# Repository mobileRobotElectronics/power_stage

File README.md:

# power-stage
Power stage designed for a mobile robot during a practical course at Karlsruhe Institute of Technology

This repository includes both the schematic and the PCD design of the power stage. Designed and edited using [KicCad7.0](https://www.kicad.org/).

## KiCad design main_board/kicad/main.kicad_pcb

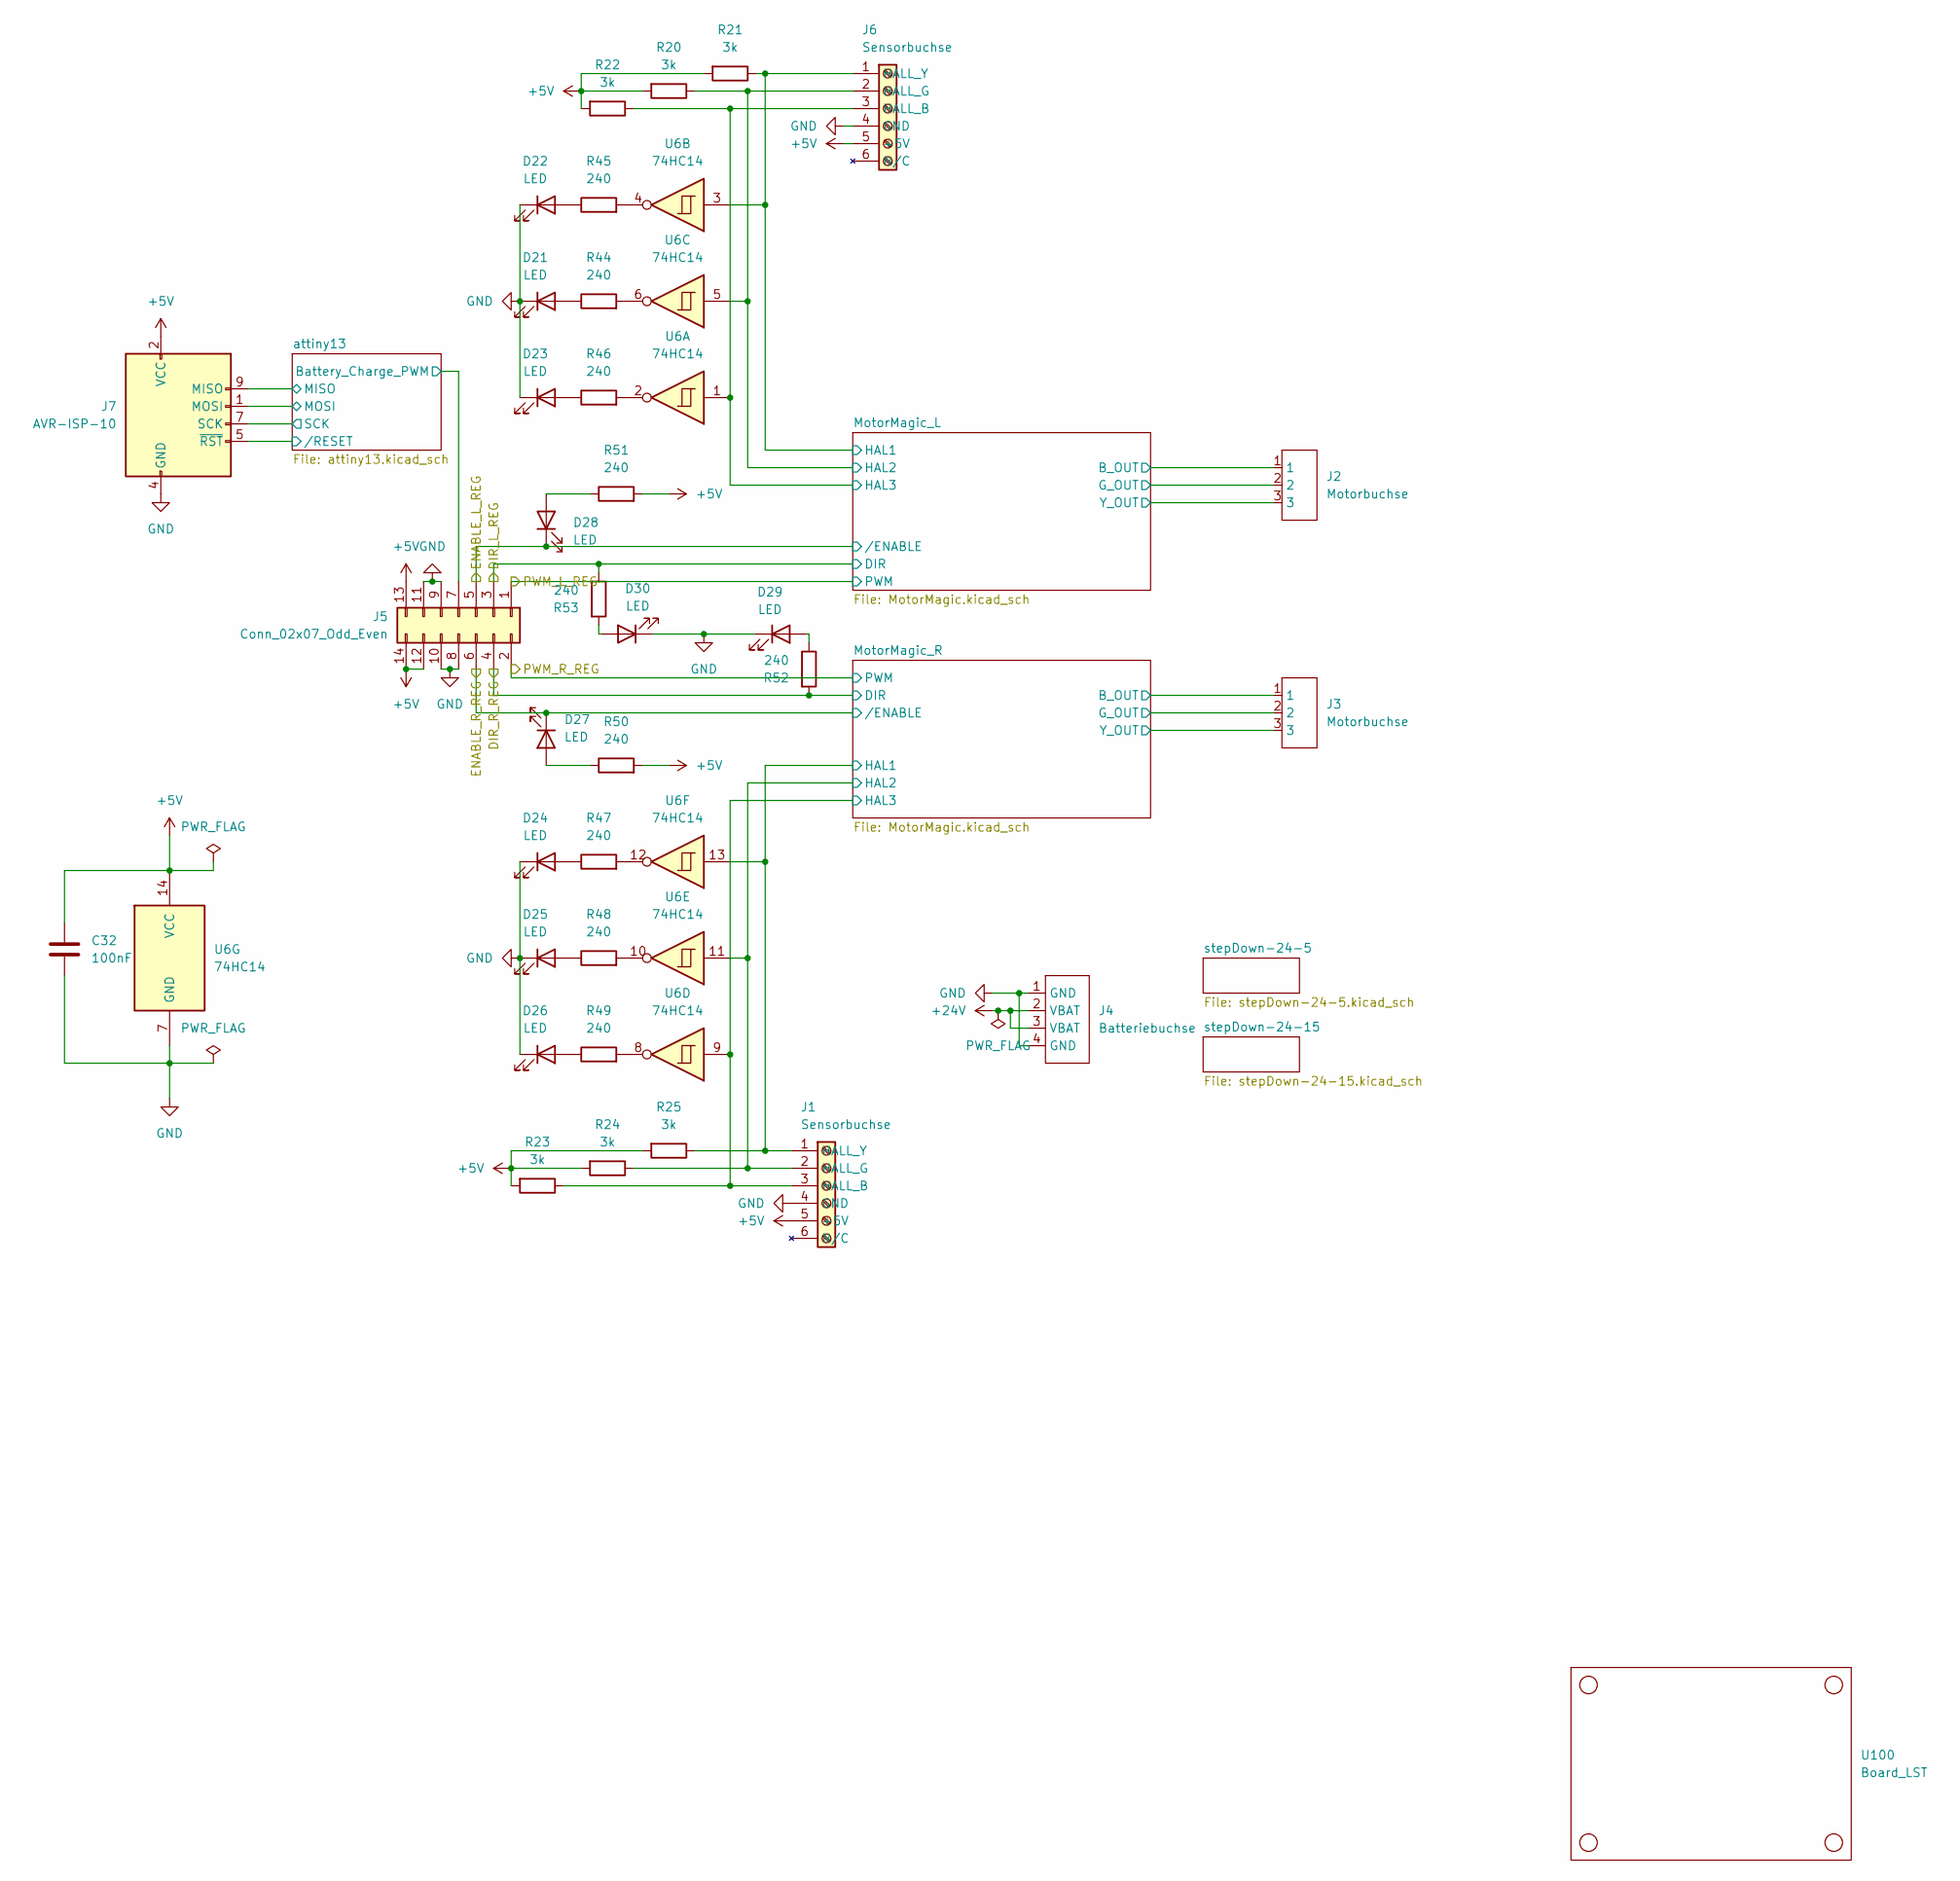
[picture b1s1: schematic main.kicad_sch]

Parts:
C32: 100nF; C_Disc_D3.0mm_W1.6mm_P2.50mm
D21, D22, D23, D24, D25, D26, D27, D28, D29, D30: LED; LED_D5.0mm
J1, J6: Sensorbuchse; PhoenixContact_MC_1,5_6-G-3.81_1x06_P3.81mm_Horizontal
J2, J3: Motorbuchse
J4: Batteriebuchse
J5: Conn_02x07_Odd_Even; IDC-Header_2x07_P2.54mm_Horizontal
J7: AVR-ISP-10; IDC-Header_2x06_P2.54mm_Horizontal
R20, R21, R22, R23, R24, R25: 3k; R_Axial_DIN0207_L6.3mm_D2.5mm_P7.62mm_Horizontal
R44, R45, R46, R47, R48, R49, R50, R51, R52, R53: 240; R_Axial_DIN0207_L6.3mm_D2.5mm_P7.62mm_Horizontal
U6: 74HC14; DIP-14_W10.16mm_LongPads
U100: Board_LST

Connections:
+24V: J4.2 (VBAT), J4.3 (VBAT); also elsewhere on the board
/DIR_L_REG: J5.3, R53.1; also elsewhere on the board
/DIR_R_REG: J5.4, R52.2; also elsewhere on the board
/ENABLE_L_REG: D28.1 (K), J5.5; also elsewhere on the board
/ENABLE_R_REG: D27.1 (K), J5.6; also elsewhere on the board
/MotorMagic_L/B_OUT: J2.1; also elsewhere on the board
/MotorMagic_L/G_OUT: J2.2; also elsewhere on the board
/MotorMagic_L/HAL1: J6.1 (HALL_Y), R21.1, U6.3; also elsewhere on the board
/MotorMagic_L/HAL2: J6.2 (HALL_G), R20.1, U6.5; also elsewhere on the board
/MotorMagic_L/HAL3: J6.3 (HALL_B), R22.1, U6.1; also elsewhere on the board
/MotorMagic_L/Y_OUT: J2.3; also elsewhere on the board
/MotorMagic_R/B_OUT: J3.1; also elsewhere on the board
/MotorMagic_R/G_OUT: J3.2; also elsewhere on the board
/MotorMagic_R/HAL1: J1.1 (HALL_Y), R25.1, U6.13; also elsewhere on the board
/MotorMagic_R/HAL2: J1.2 (HALL_G), R24.1, U6.11; also elsewhere on the board
/MotorMagic_R/HAL3: J1.3 (HALL_B), R23.1, U6.9; also elsewhere on the board
/MotorMagic_R/Y_OUT: J3.3; also elsewhere on the board
/PWM_L_REG: J5.1; also elsewhere on the board
/PWM_R_REG: J5.2; also elsewhere on the board
/attiny13/Battery_Charge_PWM: J5.7, J7.1 (MOSI); also elsewhere on the board
/attiny13/MISO: J7.9 (MISO); also elsewhere on the board
/attiny13/SCK: J7.7 (SCK); also elsewhere on the board
/attiny13//RESET: J7.5 (~RST); also elsewhere on the board
GND: C32.2, D21.1 (K), D22.1 (K), D23.1 (K), D24.1 (K), D25.1 (K), D26.1 (K), D29.1 (K), D30.1 (K), J1.4 (GND), J4.1 (GND), J4.4 (GND), J5.8, J5.9, J5.10, J5.11, J6.4 (GND), J7.4 (GND), J7.6 (GND), J7.8 (GND), J7.10 (GND), U6.7 (GND); also elsewhere on the board
unnamed: D21.2 (A), R44.1
unnamed: D22.2 (A), R45.1
unnamed: D23.2 (A), R46.1
unnamed: D24.2 (A), R47.1
unnamed: D25.2 (A), R48.1
unnamed: D26.2 (A), R49.1
unnamed: D27.2 (A), R50.1
unnamed: D28.2 (A), R51.1
unnamed: D29.2 (A), R52.1
unnamed: D30.2 (A), R53.2
unnamed: R44.2, U6.6
unnamed: R45.2, U6.4
unnamed: R46.2, U6.2
unnamed: R47.2, U6.12
unnamed: R48.2, U6.10
unnamed: R49.2, U6.8

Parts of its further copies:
C16, C22: 100nF; C_Disc_D3.0mm_W1.6mm_P2.50mm

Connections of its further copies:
GND: C16.2, C22.2; also elsewhere on the board

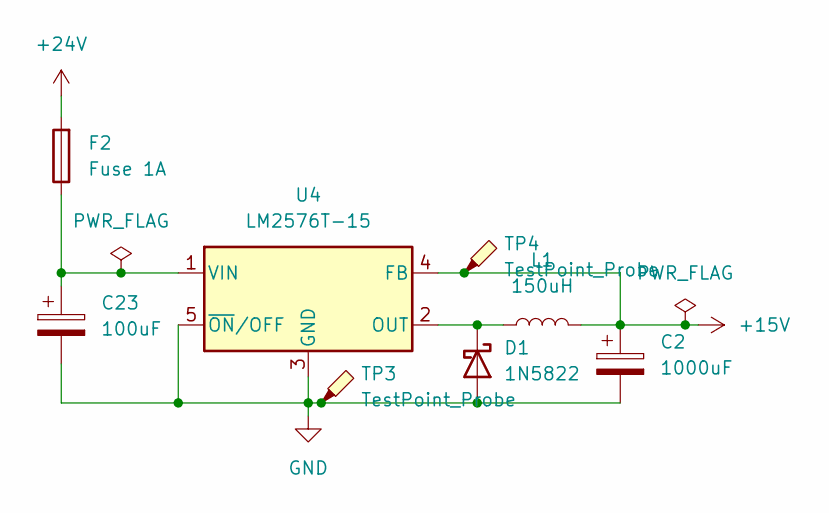
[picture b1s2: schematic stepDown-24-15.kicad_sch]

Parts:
C2: 1000uF; CP_Radial_D10.0mm_P5.00mm
C23: 100uF; CP_Radial_D6.3mm_P2.50mm
D1: 1N5822; D_DO-201AD_P15.24mm_Horizontal
F2: Fuse 1A; Fuseholder_Cylinder-5x20mm_Schurter_0031_8201_Horizontal_Op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
L1: 150uH; L_Radial_D12.5mm_P7.00mm_Fastron_09HCP
TP3, TP4: TestPoint_Probe; TestPoint_Pad_D3.0mm
U4: LM2576T-15; TO-220-5_Vertical

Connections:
+24V: F2.2; also elsewhere on the board
GND: C2.2, C23.2, D1.2 (A), TP3.1, U4.3 (GND), U4.5 (~ON/OFF); also elsewhere on the board

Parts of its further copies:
C12: 1000uF; CP_Radial_D10.0mm_P5.00mm
D5: 1N5822; D_DO-201AD_P15.24mm_Horizontal
L2: 150uH; L_Radial_D12.5mm_P7.00mm_Fastron_09HCP

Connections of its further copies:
GND: C12.2, D5.2 (A); also elsewhere on the board

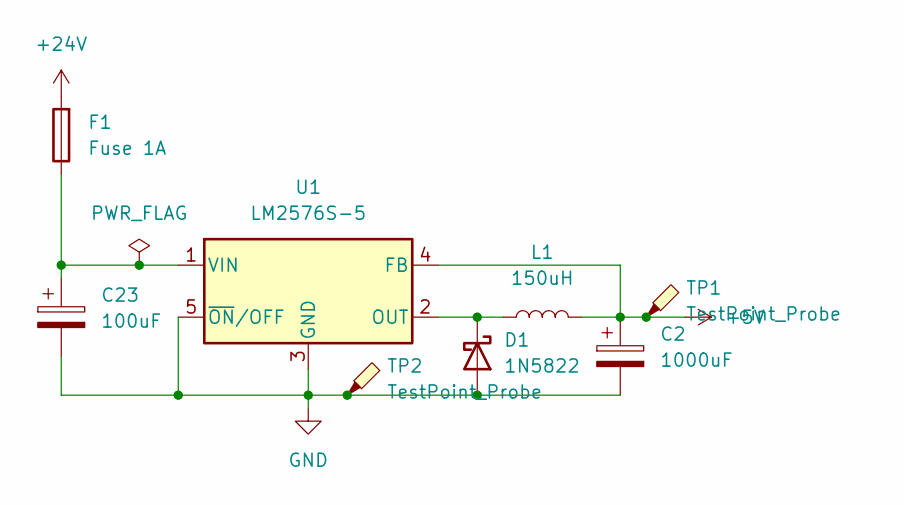
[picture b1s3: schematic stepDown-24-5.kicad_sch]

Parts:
C2: 1000uF; CP_Radial_D10.0mm_P5.00mm
C23: 100uF; CP_Radial_D6.3mm_P2.50mm
D1: 1N5822; D_DO-201AD_P15.24mm_Horizontal
F1: Fuse 1A; Fuseholder_Cylinder-5x20mm_Schurter_0031_8201_Horizontal_Op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
L1: 150uH; L_Radial_D12.5mm_P7.00mm_Fastron_09HCP
TP1, TP2: TestPoint_Probe; TestPoint_Pad_D3.0mm
U1: LM2576S-5; TO-220-5_Vertical

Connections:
+24V: F1.2; also elsewhere on the board
GND: C2.2, C23.2, D1.2 (A), TP2.1, U1.3 (GND), U1.5 (~ON/OFF); also elsewhere on the board

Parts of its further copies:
C1: 100uF; CP_Radial_D6.3mm_P2.50mm

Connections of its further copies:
GND: C1.2; also elsewhere on the board

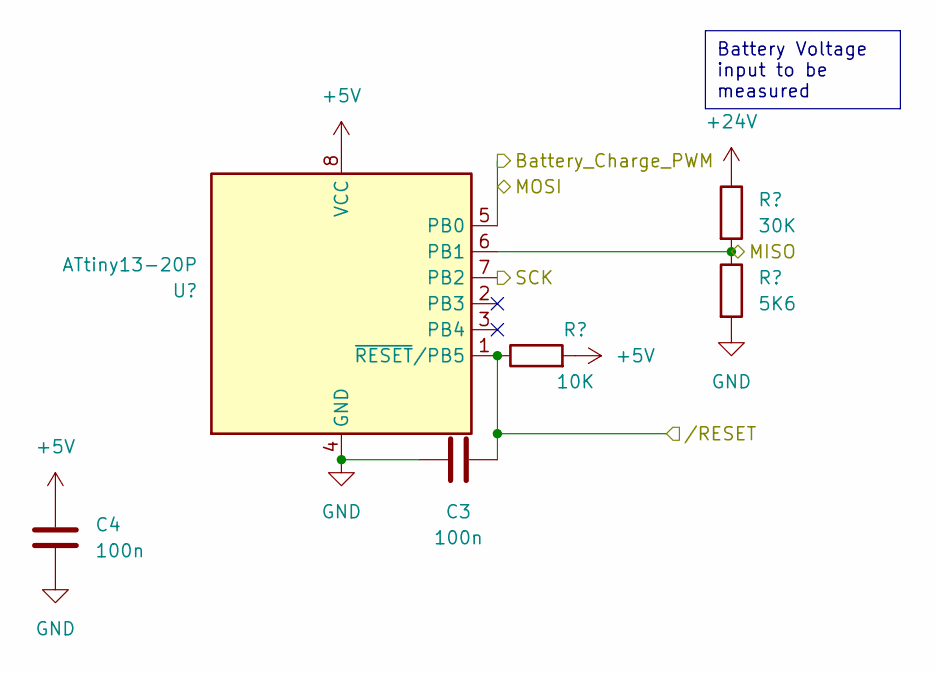
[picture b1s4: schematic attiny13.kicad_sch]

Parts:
C3, C4: 100n; C_Disc_D3.0mm_W1.6mm_P2.50mm
R1: 10K; R_Axial_DIN0207_L6.3mm_D2.5mm_P7.62mm_Horizontal
R2: 30K; R_Axial_DIN0207_L6.3mm_D2.5mm_P7.62mm_Horizontal
R3: 5K6; R_Axial_DIN0207_L6.3mm_D2.5mm_P7.62mm_Horizontal
U2: ATtiny13-20P; DIP-8_W7.62mm_LongPads

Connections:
+24V: R2.1; also elsewhere on the board
/attiny13/Battery_Charge_PWM: U2.5 (PB0); also elsewhere on the board
/attiny13/MISO: R2.2, R3.1, U2.6 (PB1); also elsewhere on the board
/attiny13/SCK: U2.7 (PB2); also elsewhere on the board
/attiny13//RESET: C3.2, R1.1, U2.1 (~RESET/PB5); also elsewhere on the board
GND: C3.1, C4.2, R3.2, U2.4 (GND); also elsewhere on the board

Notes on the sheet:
Battery Voltage input to be measured

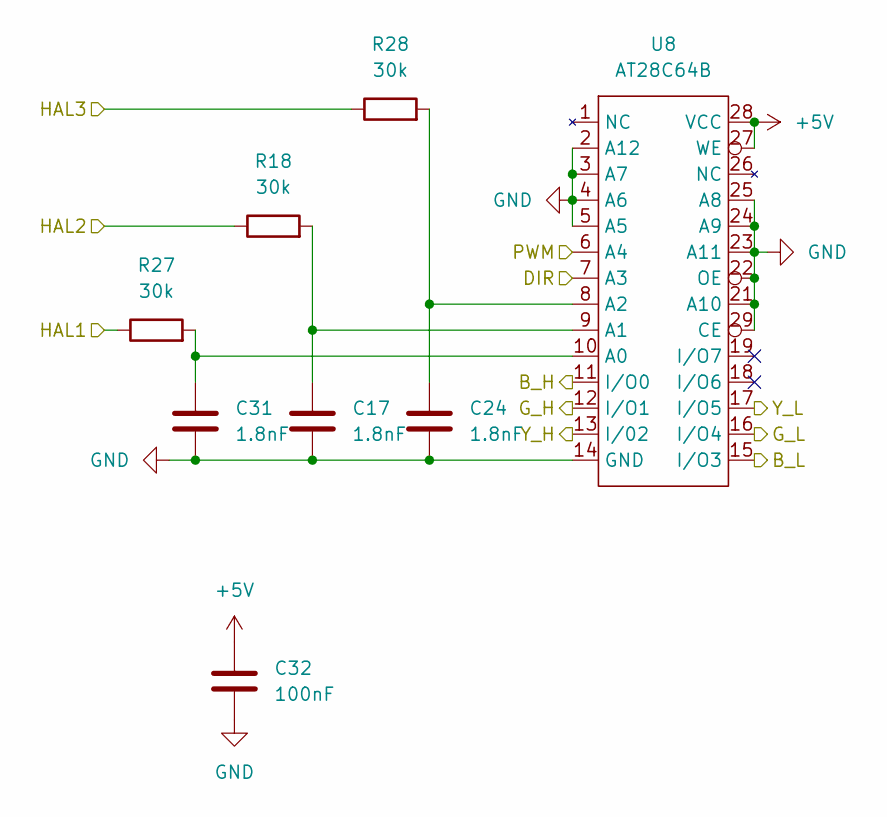
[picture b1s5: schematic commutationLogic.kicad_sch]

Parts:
C17, C24, C31: 1.8nF; C_Disc_D6.0mm_W2.5mm_P5.00mm
C32: 100nF; C_Disc_D3.0mm_W1.6mm_P2.50mm
R18, R27, R28: 30k; R_Axial_DIN0207_L6.3mm_D2.5mm_P7.62mm_Horizontal
U8: AT28C64B; DIP-28_W15.24mm_Socket_LongPads

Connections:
/DIR_L_REG: U8.7 (A3); also elsewhere on the board
/MotorMagic_L/HAL1: R27.1; also elsewhere on the board
/MotorMagic_L/HAL2: R18.1; also elsewhere on the board
/MotorMagic_L/HAL3: R28.1; also elsewhere on the board
/MotorMagic_L/bridgeDriver2/B_H_IN: U8.11 (I/O0); also elsewhere on the board
/MotorMagic_L/bridgeDriver2/B_L_IN: U8.15 (I/O3); also elsewhere on the board
/MotorMagic_L/bridgeDriver2/G_H_IN: U8.12 (I/O1); also elsewhere on the board
/MotorMagic_L/bridgeDriver2/G_L_IN: U8.16 (I/O4); also elsewhere on the board
/MotorMagic_L/bridgeDriver2/Y_H_IN: U8.13 (I/02); also elsewhere on the board
/MotorMagic_L/bridgeDriver2/Y_L_IN: U8.17 (I/O5); also elsewhere on the board
/PWM_L_REG: U8.6 (A4); also elsewhere on the board
GND: C17.2, C24.2, C31.2, C32.2, U8.2 (A12), U8.3 (A7), U8.4 (A6), U8.5 (A5), U8.14 (GND), U8.21 (A10), U8.22 (OE), U8.23 (A11), U8.24 (A9), U8.25 (A8), U8.29 (CE); also elsewhere on the board
unnamed: C31.1, R27.2, U8.10 (A0)
unnamed: C17.1, R18.2, U8.9 (A1)
unnamed: C24.1, R28.2, U8.8 (A2)

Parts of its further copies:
C11, C15, C20: 1.8nF; C_Disc_D6.0mm_W2.5mm_P5.00mm
C16: 100nF; C_Disc_D3.0mm_W1.6mm_P2.50mm
R17, R19, R26: 30k; R_Axial_DIN0207_L6.3mm_D2.5mm_P7.62mm_Horizontal
U5: AT28C64B; DIP-28_W15.24mm_Socket_LongPads

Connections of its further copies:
/DIR_R_REG: U5.7 (A3); also elsewhere on the board
/MotorMagic_R/HAL1: R26.1; also elsewhere on the board
/MotorMagic_R/HAL2: R17.1; also elsewhere on the board
/MotorMagic_R/HAL3: R19.1; also elsewhere on the board
/MotorMagic_R/bridgeDriver2/B_H_IN: U5.11 (I/O0); also elsewhere on the board
/MotorMagic_R/bridgeDriver2/B_L_IN: U5.15 (I/O3); also elsewhere on the board
/MotorMagic_R/bridgeDriver2/G_H_IN: U5.12 (I/O1); also elsewhere on the board
/MotorMagic_R/bridgeDriver2/G_L_IN: U5.16 (I/O4); also elsewhere on the board
/MotorMagic_R/bridgeDriver2/Y_H_IN: U5.13 (I/02); also elsewhere on the board
/MotorMagic_R/bridgeDriver2/Y_L_IN: U5.17 (I/O5); also elsewhere on the board
/PWM_R_REG: U5.6 (A4); also elsewhere on the board
GND: C11.2, C15.2, C16.2, C20.2, U5.2 (A12), U5.3 (A7), U5.4 (A6), U5.5 (A5), U5.14 (GND), U5.21 (A10), U5.22 (OE), U5.23 (A11), U5.24 (A9), U5.25 (A8); also elsewhere on the board
unnamed: C15.1, R26.2, U5.10 (A0)
unnamed: C11.1, R17.2, U5.9 (A1)
unnamed: C20.1, R19.2, U5.8 (A2)

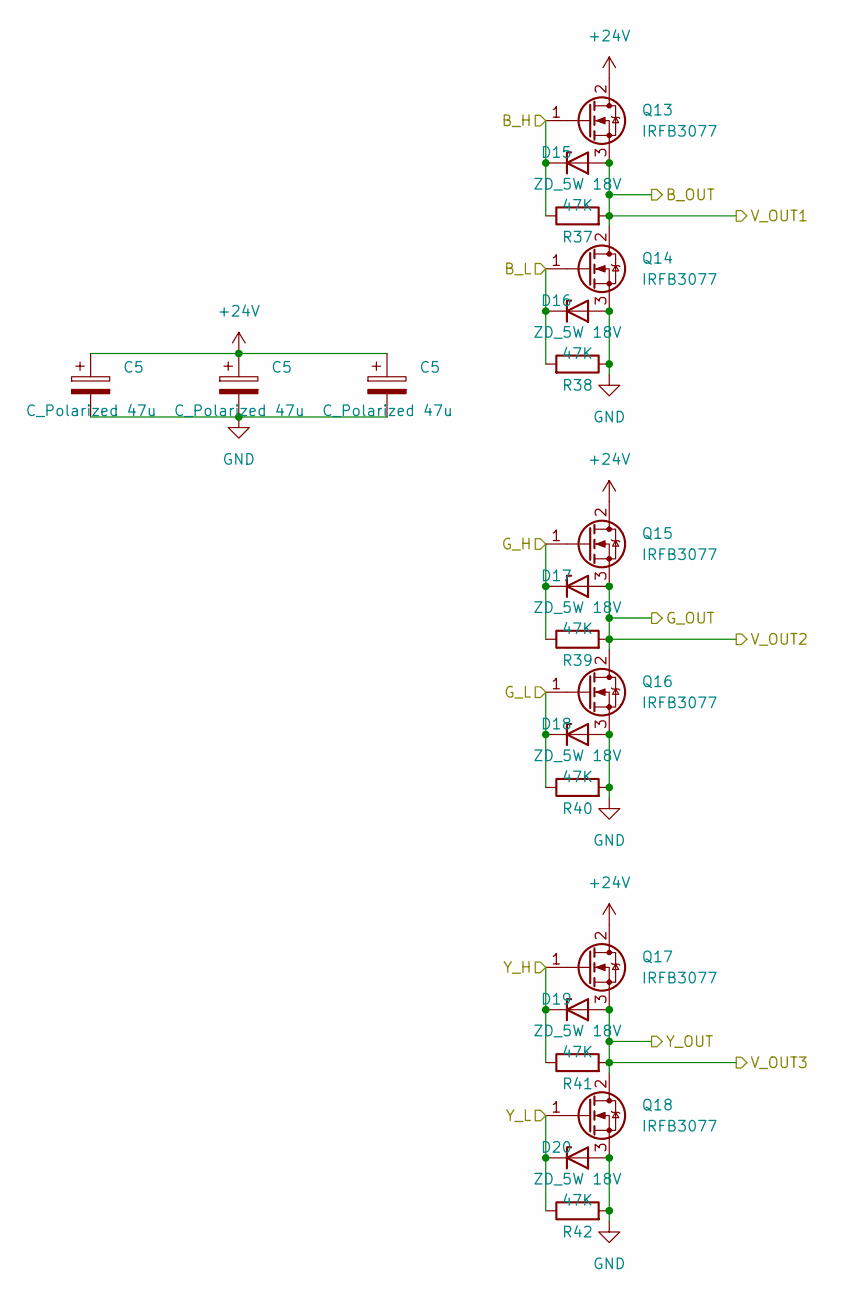
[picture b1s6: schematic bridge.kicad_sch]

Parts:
C5: C_Polarized 47u; CP_Radial_D8.0mm_P3.50mm
D15, D16, D17, D18, D19, D20: ZD_5W 18V; D_DO-201_P15.24mm_Horizontal
Q13, Q14, Q15, Q16, Q17, Q18: IRFB3077; TO-220-3_Vertical
R37, R38, R39, R40, R41, R42: 47K; R_Axial_DIN0207_L6.3mm_D2.5mm_P7.62mm_Horizontal

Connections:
+24V: C5.1, Q13.2 (D), Q15.2 (D), Q17.2 (D); also elsewhere on the board
/MotorMagic_L/B_OUT: D15.2 (A), Q13.3 (S), Q14.2 (D), R37.2; also elsewhere on the board
/MotorMagic_L/G_OUT: D17.2 (A), Q15.3 (S), Q16.2 (D), R39.2; also elsewhere on the board
/MotorMagic_L/Y_OUT: D19.2 (A), Q17.3 (S), Q18.2 (D), R41.2; also elsewhere on the board
/MotorMagic_L/bridge2/B_H: D15.1 (K), Q13.1 (G), R37.1; also elsewhere on the board
/MotorMagic_L/bridge2/B_L: D16.1 (K), Q14.1 (G), R38.2; also elsewhere on the board
/MotorMagic_L/bridge2/G_H: D17.1 (K), Q15.1 (G), R39.1; also elsewhere on the board
/MotorMagic_L/bridge2/G_L: D18.1 (K), Q16.1 (G), R40.1; also elsewhere on the board
/MotorMagic_L/bridge2/Y_H: D19.1 (K), Q17.1 (G), R41.1; also elsewhere on the board
/MotorMagic_L/bridge2/Y_L: D20.1 (K), Q18.1 (G), R42.1; also elsewhere on the board
GND: C5.2, D16.2 (A), D18.2 (A), D20.2 (A), Q14.3 (S), Q16.3 (S), Q18.3 (S), R38.1, R40.2, R42.2; also elsewhere on the board

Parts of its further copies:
C6, C7, C40, C41, C42: C_Polarized 47u; CP_Radial_D8.0mm_P3.50mm
D2, D3, D4, D6, D7, D8: ZD_5W 18V; D_DO-201_P15.24mm_Horizontal
Q1, Q2, Q3, Q4, Q5, Q6: IRFB3077; TO-220-3_Vertical
R4, R5, R6, R7, R8, R9: 47K; R_Axial_DIN0207_L6.3mm_D2.5mm_P7.62mm_Horizontal

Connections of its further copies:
+24V: C6.1, C7.1, C40.1, C41.1, C42.1, Q1.2 (D), Q3.2 (D), Q5.2 (D); also elsewhere on the board
/MotorMagic_R/B_OUT: D2.2 (A), Q1.3 (S), Q2.2 (D), R4.2; also elsewhere on the board
/MotorMagic_R/G_OUT: D4.2 (A), Q3.3 (S), Q4.2 (D), R9.2; also elsewhere on the board
/MotorMagic_R/Y_OUT: D7.2 (A), Q5.3 (S), Q6.2 (D), R6.2; also elsewhere on the board
/MotorMagic_R/bridge2/B_H: D2.1 (K), Q1.1 (G), R4.1; also elsewhere on the board
/MotorMagic_R/bridge2/B_L: D3.1 (K), Q2.1 (G), R8.2; also elsewhere on the board
/MotorMagic_R/bridge2/G_H: D4.1 (K), Q3.1 (G), R9.1; also elsewhere on the board
/MotorMagic_R/bridge2/G_L: D6.1 (K), Q4.1 (G), R5.1; also elsewhere on the board
/MotorMagic_R/bridge2/Y_H: D7.1 (K), Q5.1 (G), R6.1; also elsewhere on the board
/MotorMagic_R/bridge2/Y_L: D8.1 (K), Q6.1 (G), R7.1; also elsewhere on the board
GND: C6.2, C7.2, C40.2, C41.2, C42.2, D3.2 (A), D6.2 (A), D8.2 (A), Q2.3 (S), Q4.3 (S), Q6.3 (S), R5.2, R7.2, R8.1; also elsewhere on the board

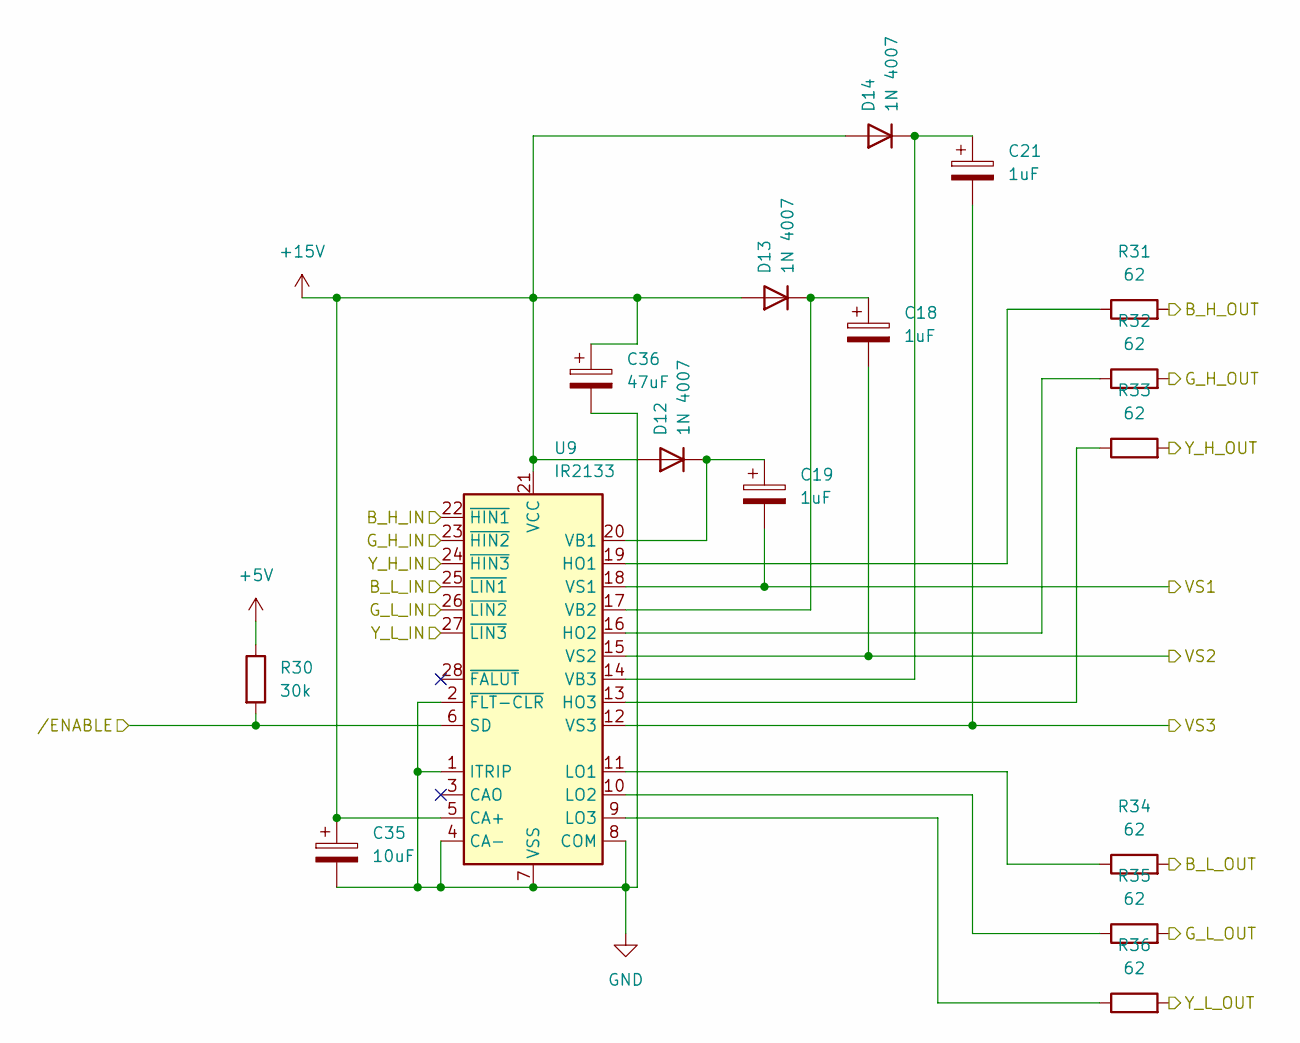
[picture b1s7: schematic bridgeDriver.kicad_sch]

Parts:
C18, C19, C21: 1uF; CP_Radial_D5.0mm_P2.00mm
C35: 10uF; CP_Radial_D5.0mm_P2.00mm
C36: 47uF; CP_Radial_D8.0mm_P3.50mm
D12, D13, D14: 1N 4007; D_DO-41_SOD81_P7.62mm_Horizontal
R30: 30k; R_Axial_DIN0207_L6.3mm_D2.5mm_P7.62mm_Horizontal
R31, R32, R33, R34, R35, R36: 62; R_Axial_DIN0207_L6.3mm_D2.5mm_P7.62mm_Horizontal
U9: IR2133; DIP-28_W15.24mm_Socket_LongPads

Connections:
/ENABLE_L_REG: R30.2, U9.6 (SD); also elsewhere on the board
/MotorMagic_L/B_OUT: C19.2, U9.18 (VS1); also elsewhere on the board
/MotorMagic_L/G_OUT: C18.2, U9.15 (VS2); also elsewhere on the board
/MotorMagic_L/Y_OUT: C21.2, U9.12 (VS3); also elsewhere on the board
/MotorMagic_L/bridge2/B_H: R31.2; also elsewhere on the board
/MotorMagic_L/bridge2/B_L: R34.2; also elsewhere on the board
/MotorMagic_L/bridge2/G_H: R32.2; also elsewhere on the board
/MotorMagic_L/bridge2/G_L: R35.2; also elsewhere on the board
/MotorMagic_L/bridge2/Y_H: R33.2; also elsewhere on the board
/MotorMagic_L/bridge2/Y_L: R36.2; also elsewhere on the board
/MotorMagic_L/bridgeDriver2/B_H_IN: U9.22 (~HIN1); also elsewhere on the board
/MotorMagic_L/bridgeDriver2/B_L_IN: U9.25 (~LIN1); also elsewhere on the board
/MotorMagic_L/bridgeDriver2/G_H_IN: U9.23 (~HIN2); also elsewhere on the board
/MotorMagic_L/bridgeDriver2/G_L_IN: U9.26 (~LIN2); also elsewhere on the board
/MotorMagic_L/bridgeDriver2/Y_H_IN: U9.24 (~HIN3); also elsewhere on the board
/MotorMagic_L/bridgeDriver2/Y_L_IN: U9.27 (~LIN3); also elsewhere on the board
GND: C35.2, C36.2, U9.1 (ITRIP), U9.2 (~FLT-CLR), U9.4 (CA-), U9.7 (VSS), U9.8 (COM); also elsewhere on the board
unnamed: C19.1, D12.1 (K), U9.20 (VB1)
unnamed: C18.1, D13.1 (K), U9.17 (VB2)
unnamed: C21.1, D14.1 (K), U9.14 (VB3)
unnamed: R31.1, U9.19 (HO1)
unnamed: R32.1, U9.16 (HO2)
unnamed: R33.1, U9.13 (HO3)
unnamed: R34.1, U9.11 (LO1)
unnamed: R35.1, U9.10 (LO2)
unnamed: R36.1, U9.9 (LO3)

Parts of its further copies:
C8: 10uF; CP_Radial_D5.0mm_P2.00mm
C9: 47uF; CP_Radial_D8.0mm_P3.50mm
C10, C13, C14: 1uF; CP_Radial_D5.0mm_P2.00mm
D9, D10, D11: 1N 4007; D_DO-41_SOD81_P7.62mm_Horizontal
R10: 30k; R_Axial_DIN0207_L6.3mm_D2.5mm_P7.62mm_Horizontal
R11, R12, R13, R14, R15, R16: 62; R_Axial_DIN0207_L6.3mm_D2.5mm_P7.62mm_Horizontal
U3: IR2133; DIP-28_W15.24mm_Socket_LongPads

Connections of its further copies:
/ENABLE_R_REG: R10.2, U3.6 (SD); also elsewhere on the board
/MotorMagic_R/B_OUT: C10.2, U3.18 (VS1); also elsewhere on the board
/MotorMagic_R/G_OUT: C13.2, U3.15 (VS2); also elsewhere on the board
/MotorMagic_R/Y_OUT: C14.2, U3.12 (VS3); also elsewhere on the board
/MotorMagic_R/bridge2/B_H: R11.2; also elsewhere on the board
/MotorMagic_R/bridge2/B_L: R14.2; also elsewhere on the board
/MotorMagic_R/bridge2/G_H: R12.2; also elsewhere on the board
/MotorMagic_R/bridge2/G_L: R15.2; also elsewhere on the board
/MotorMagic_R/bridge2/Y_H: R13.2; also elsewhere on the board
/MotorMagic_R/bridge2/Y_L: R16.2; also elsewhere on the board
/MotorMagic_R/bridgeDriver2/B_H_IN: U3.22 (~HIN1); also elsewhere on the board
/MotorMagic_R/bridgeDriver2/B_L_IN: U3.25 (~LIN1); also elsewhere on the board
/MotorMagic_R/bridgeDriver2/G_H_IN: U3.23 (~HIN2); also elsewhere on the board
/MotorMagic_R/bridgeDriver2/G_L_IN: U3.26 (~LIN2); also elsewhere on the board
/MotorMagic_R/bridgeDriver2/Y_H_IN: U3.24 (~HIN3); also elsewhere on the board
/MotorMagic_R/bridgeDriver2/Y_L_IN: U3.27 (~LIN3); also elsewhere on the board
GND: C8.2, C9.2, U3.1 (ITRIP), U3.2 (~FLT-CLR), U3.4 (CA-), U3.7 (VSS), U3.8 (COM); also elsewhere on the board
unnamed: C10.1, D9.1 (K), U3.20 (VB1)
unnamed: C13.1, D10.1 (K), U3.17 (VB2)
unnamed: C14.1, D11.1 (K), U3.14 (VB3)
unnamed: R11.1, U3.19 (HO1)
unnamed: R12.1, U3.16 (HO2)
unnamed: R13.1, U3.13 (HO3)
unnamed: R14.1, U3.11 (LO1)
unnamed: R15.1, U3.10 (LO2)
unnamed: R16.1, U3.9 (LO3)

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
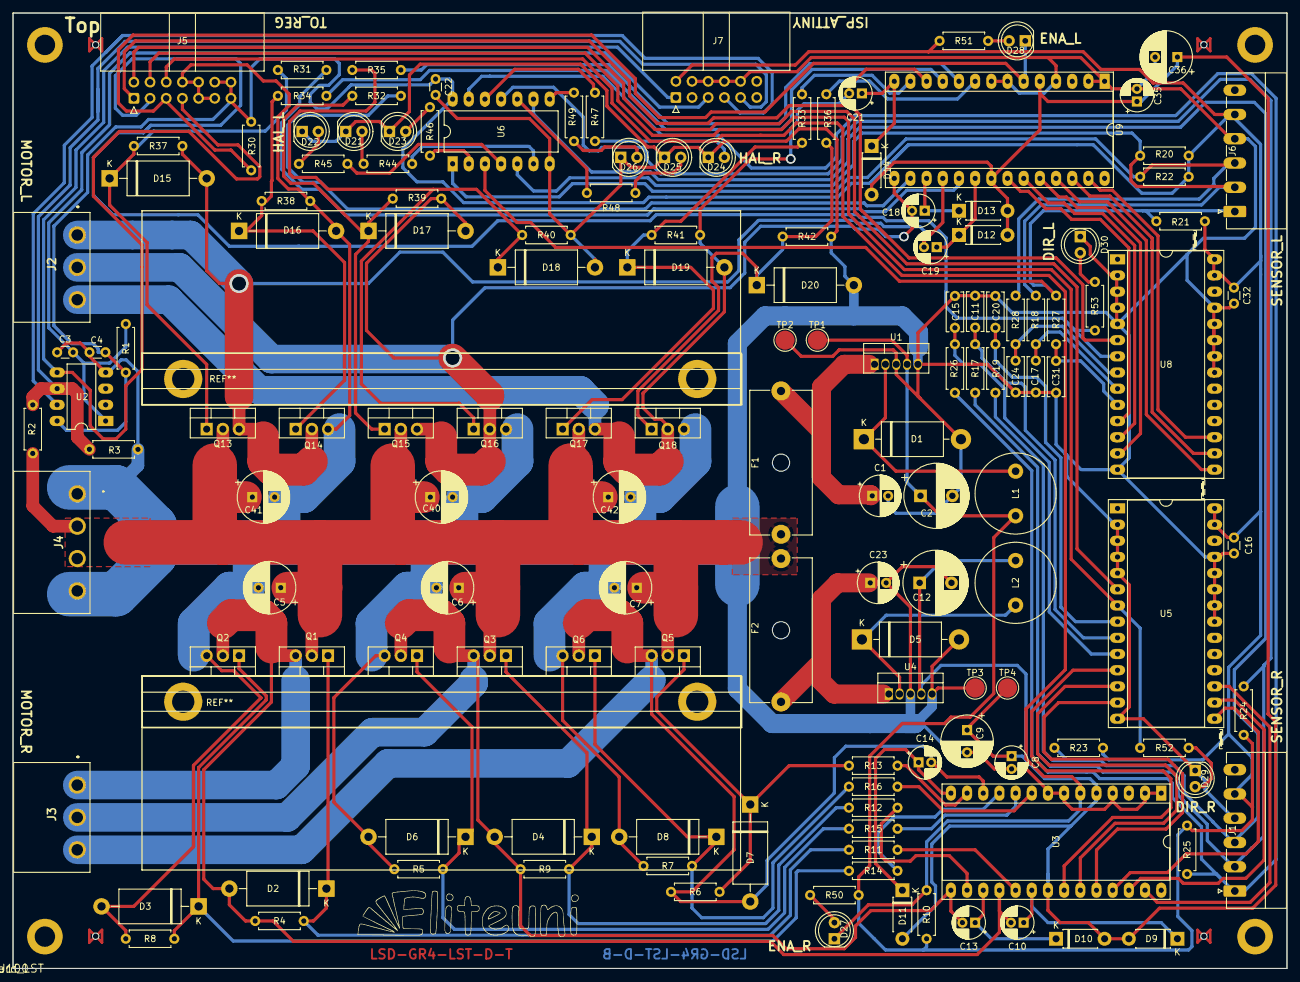
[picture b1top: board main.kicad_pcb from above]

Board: 2 copper layers, 200.0 x 150.0 mm, 148 parts (0 on the bottom side), 94 nets.

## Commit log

2023-10-02 added verilog implementation of commutation multiplexer
2023-10-02 started work on main board
2023-10-02 started bridge design
2023-10-02 changes to bridge design
2023-10-04 added bridge driver stub
2023-10-04 bridge driver almost done
2023-10-04 added hierarchy for 15v stepdown
2023-10-04 implemented 15v stepdown
2023-10-04 added communication logic
2023-10-04 added cancel diodes and pullup to bridge
2023-10-04 added isp interface to attiny
2023-10-04 revamped root and bridge
2023-10-04 added ISP socket for attiny
2023-10-04 added pull up resistor values
2023-10-04 fixed pull up resistor values
2023-10-04 added funny fun file
2023-10-04 added component values
2023-10-04 added bridge driver values
2023-10-04 added component values to bridge
2023-10-04 added eeprom values
2023-10-04 added first capacitor value for stepdown
2023-10-05 renamed motor magic file
2023-10-05 added LEDS and fuses
2023-10-05 resolved ERC
2023-10-05 added probe point
2023-10-05 updated to post review state
2023-10-05 corrected issues detected in review
2023-10-06 added footprints
2023-10-06 moved commutation mux stuff to commutationdmux repo
2023-10-06 implemented bridge and first bridge driver as well as both step converters on the pcd layout
2023-10-07 rerouted some lines, also added attiny
2023-10-07 rerouted some lines
2023-10-07 rerouted lines
2023-10-07 installed REG connector
2023-10-07 rerouted more lines, also implemented HAL LEDS
2023-10-07 added text markers
2023-10-08 moved logic sockets
2023-10-08 optimization
2023-10-09 more optimization
2023-10-09 solved DRC
2023-10-09 finalized board
2023-10-26 added images and additional information to readme
